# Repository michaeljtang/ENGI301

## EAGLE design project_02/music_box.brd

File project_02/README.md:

# Project 02

Project 02 involves creating a PCB for the programmable music box implemented and described in the ENGI301/project01 folder in this repo. More specifically, the PCB created is intended to host all components (or connectors to components, if they are too big) necessary for the programmable music box to run. 

In addition to a Bill-of-Materials and and PCB Schematic, this directory contains the following folders:

### /EAGLE
This folder contains the Eagle files of my PCB, and include schematic, board, as well as a library with all parts used.

### /MFG
This folder contains all the Gerber manufacturing files needed to actually manufacture my PCB

### /docs
This folder contains documentation relevant in the planning of my PCB, as well as images of the top and bottom views of my PCB (per the Gerber files).

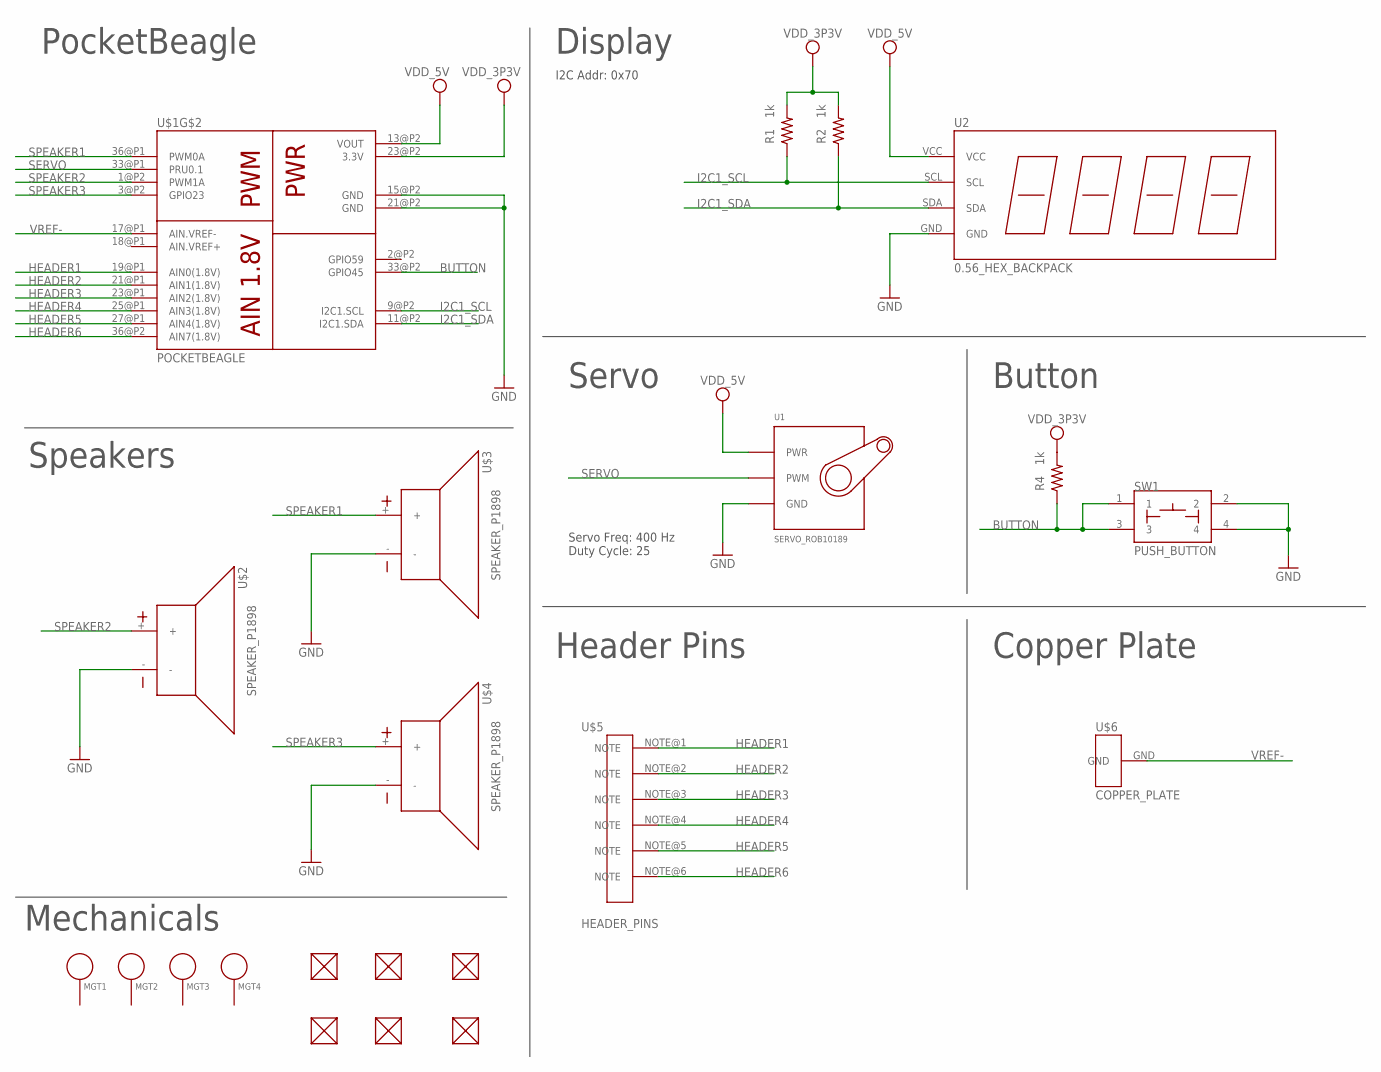
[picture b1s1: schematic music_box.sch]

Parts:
FUD1, FUD2, FUD3, FUD4, FUD5, FUD6: FIDUCIAL; FIDUCIAL_40MIL
MGT1, MGT2, MGT3, MGT4: MOUNTING_HOLE
R1, R2, R4: 1k; R0603
SW1: PUSH_BUTTON; BUTTON_12.5MM
U1: SERVO_ROB10189; SERVO-X1
U2: 0.56_HEX_BACKPACK
U$1: POCKETBEAGLE
U$2, U$3, U$4: SPEAKER_P1898; SPEAKER
U$5: HEADER_PINS
U$6: COPPER_PLATE

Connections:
BUTTON: R4.1, SW1.1, SW1.3, U$1.33@P2 (GPIO45)
GND: SW1.2, SW1.4, U1.GND, U2.GND, U$1.15@P2 (GND), U$1.21@P2 (GND), U$2.-, U$3.-, U$4.-
HEADER1: U$1.19@P1 (AIN0(1.8V)), U$5.NOTE@1
HEADER2: U$1.21@P1 (AIN1(1.8V)), U$5.NOTE@2
HEADER3: U$1.23@P1 (AIN2(1.8V)), U$5.NOTE@3
HEADER4: U$1.25@P1 (AIN3(1.8V)), U$5.NOTE@4
HEADER5: U$1.27@P1 (AIN4(1.8V)), U$5.NOTE@5
HEADER6: U$1.36@P2 (AIN7(1.8V)), U$5.NOTE@6
I2C1_SCL: R1.1, U2.SCL, U$1.9@P2 (I2C1.SCL)
I2C1_SDA: R2.1, U2.SDA, U$1.11@P2 (I2C1.SDA)
SERVO: U1.SIG (PWM), U$1.33@P1 (PRU0.1)
SPEAKER1: U$1.36@P1 (PWM0A), U$3.+
SPEAKER2: U$1.1@P2 (PWM1A), U$2.+
SPEAKER3: U$1.3@P2 (GPIO23), U$4.+
VDD_3P3V: R1.2, R2.2, R4.2, U$1.23@P2 (3.3V)
VDD_5V: U1.PWR, U2.VCC, U$1.13@P2 (VOUT)
VREF-: U$1.17@P1 (AIN.VREF-), U$6.GND

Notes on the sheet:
PocketBeagle
Display
Servo
Button
Header Pins
Copper Plate
Speakers
I2C Addr: 0x70
Servo Freq: 400 Hz Duty Cycle: 25
Mechanicals

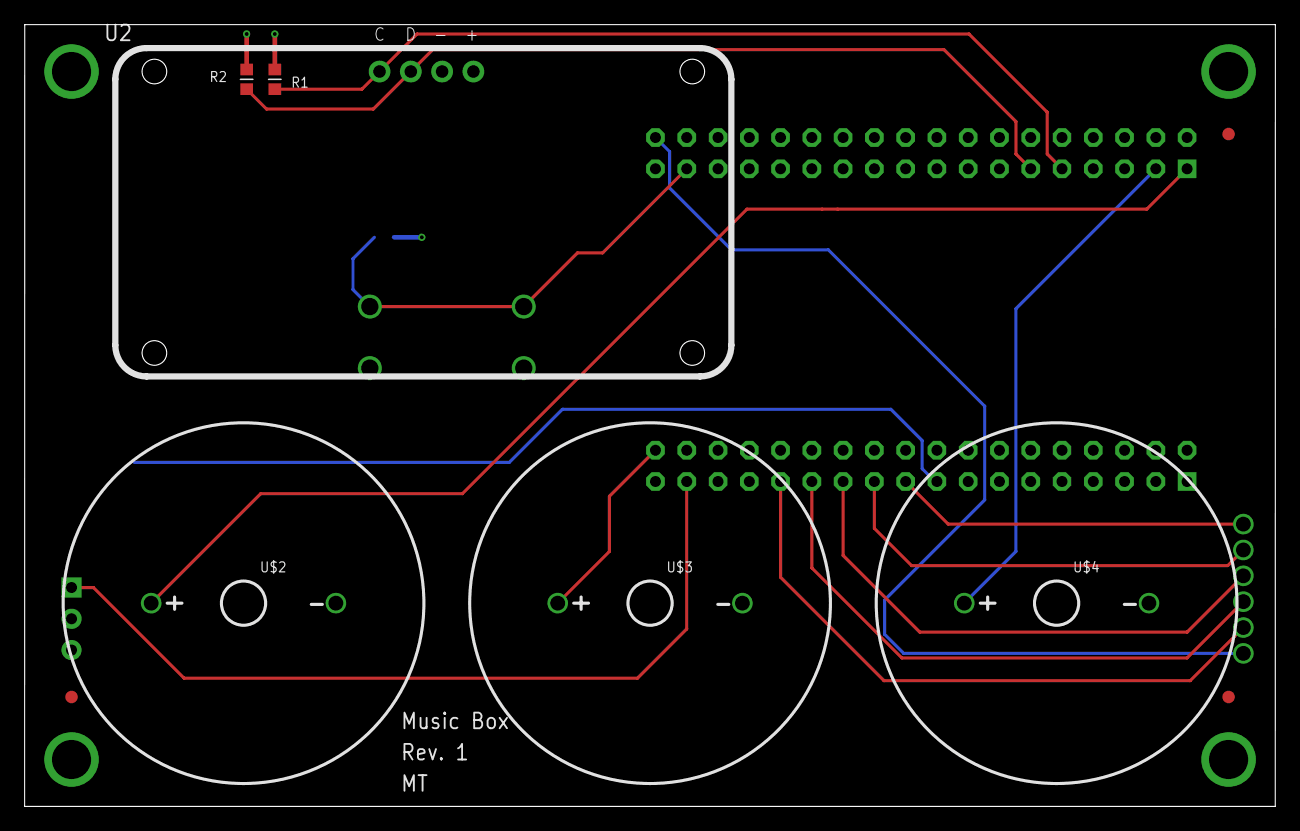
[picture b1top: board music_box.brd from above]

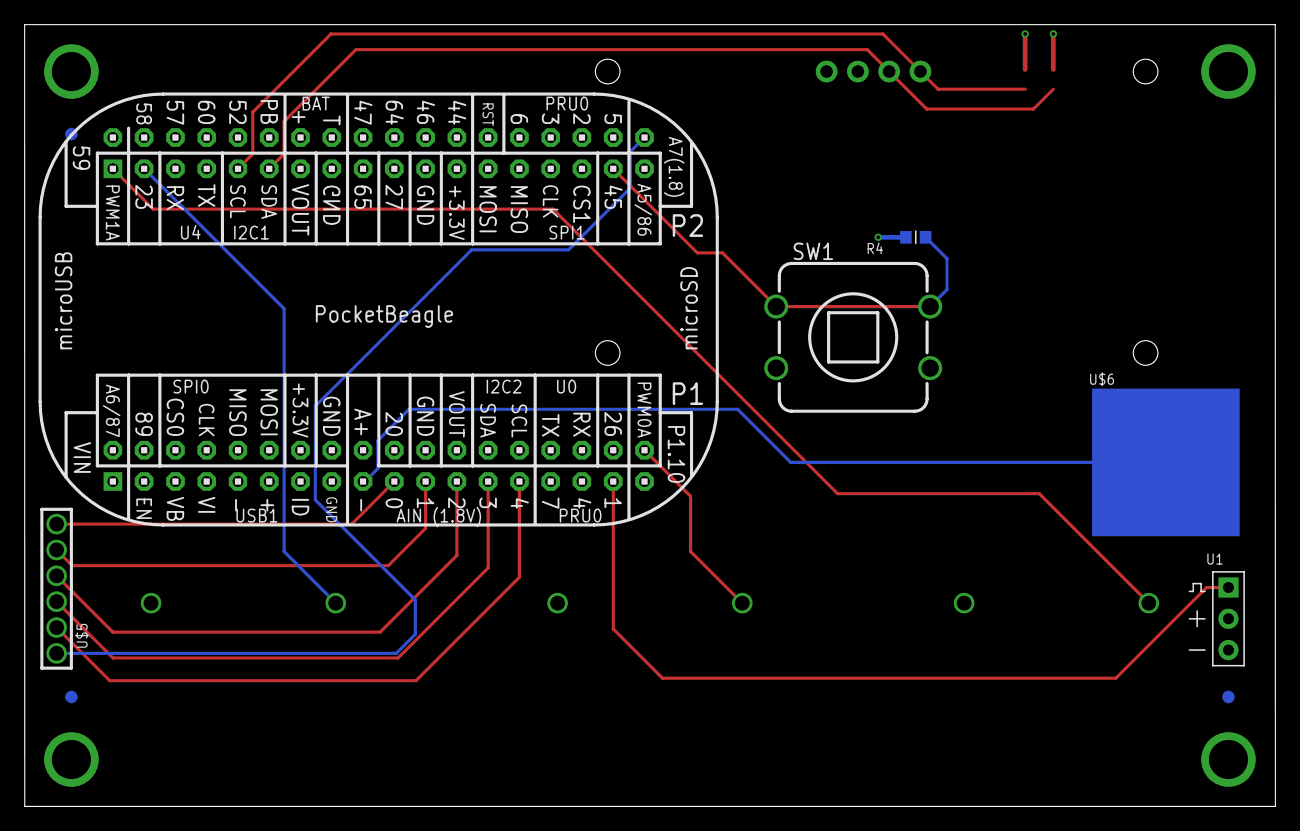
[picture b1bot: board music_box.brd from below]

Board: 4 copper layers, 101.6 x 63.5 mm, 22 parts (9 on the bottom side), 17 nets.

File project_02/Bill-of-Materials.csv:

Qty,Manufacturer/MPN,Value             ,Device            ,Package           ,Parts/Designator,Description                                    
1,Adafruit HT16K33,0.56_HEX_BACKPACK ,0.56_HEX_BACKPACK ,0.56_HEX_BACKPACK ,U2                                 ,"0.56"" LED HEX Backback - Adafruit HT16K33 -"
3,MF-RES-0603-1K,1k                ,R_R0603           ,R0603             ,"R1, R2, R4","RESISTOR, American symbol"
1,N/A,COPPER_PLATE      ,COPPER_PLATE      ,COPPER_PLATE      ,U$6,Copper plate to serve as a grounded surface
6,N/A,FIDUCIAL          ,FIDUCIAL          ,FIDUCIAL_40MIL    ,"FUD1, FUD2, FUD3, FUD4, FUD5, FUD6",Fiducials to aid PCB manufacturing
1,N/A,HEADER_PINS       ,HEADER_PINS       ,HEADER_PINS       ,U$5,Standard Header Pins to act as floating analog inputs
4,N/A,MOUNTING_HOLE     ,MOUNTING_HOLE     ,MOUNTING_HOLE     ,"MGT1, MGT2, MGT3, MGT4",Chassis Mounting Hole w/GND connection ability
1,BeagleBoard,POCKETBEAGLE      ,POCKETBEAGLE      ,POCKETBEAGLE      ,U$1,Microcontroller running 1GHz ARM Cortex-A8
1,Gikfun LYSB01E38OS7K-ELECTRNCS,PUSH_BUTTON       ,PUSH_BUTTON       ,BUTTON_12.5MM     ,SW1                                                                               ,Standard 12x12x7.3 mm Push Button
1,Sparkfun ROB10189,SERVO_ROB10189    ,SERVO_ROB10190,SERVO-X1          ,U1                                                                                ,Continuous Rotation Servo (Micro-Size)
3,Adafruit P1898,SPEAKER_P1898     ,SPEAKER_P1899,SPEAKER           ,"U$2, U$3, U$4",PCB Mount Mini Speaker

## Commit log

2020-09-14 Updating README.md
2020-09-29 added python 2/3 functionality
2020-09-29 fixed documentation
2020-09-29 fixed typos
2020-11-04 added 7-seg display
2020-11-04 adding button
2020-11-07 deleted files
2020-11-07 added button
2020-11-07 added motor functionality
2020-11-07 changed a couple ins
2020-11-07 fixed motor
2020-11-08 added keyboard interrupt
2020-11-08 fixed button functionality
2020-11-08 fixed on/off functionality
2020-11-08 fixed interaction with motor.py
2020-11-08 fixed interface with speakers
2020-11-08 fixed error with frequency dict
2020-11-08 added documentation
2020-11-12 fixed pins
2020-11-12 removed file
2020-11-13 updated diagrams
2020-11-13 Fixed minor typo in comment
2020-11-13 Fixed minor typo in comments
2020-12-17 removed
2020-12-17 finished layout
2020-12-17 moved around columns
